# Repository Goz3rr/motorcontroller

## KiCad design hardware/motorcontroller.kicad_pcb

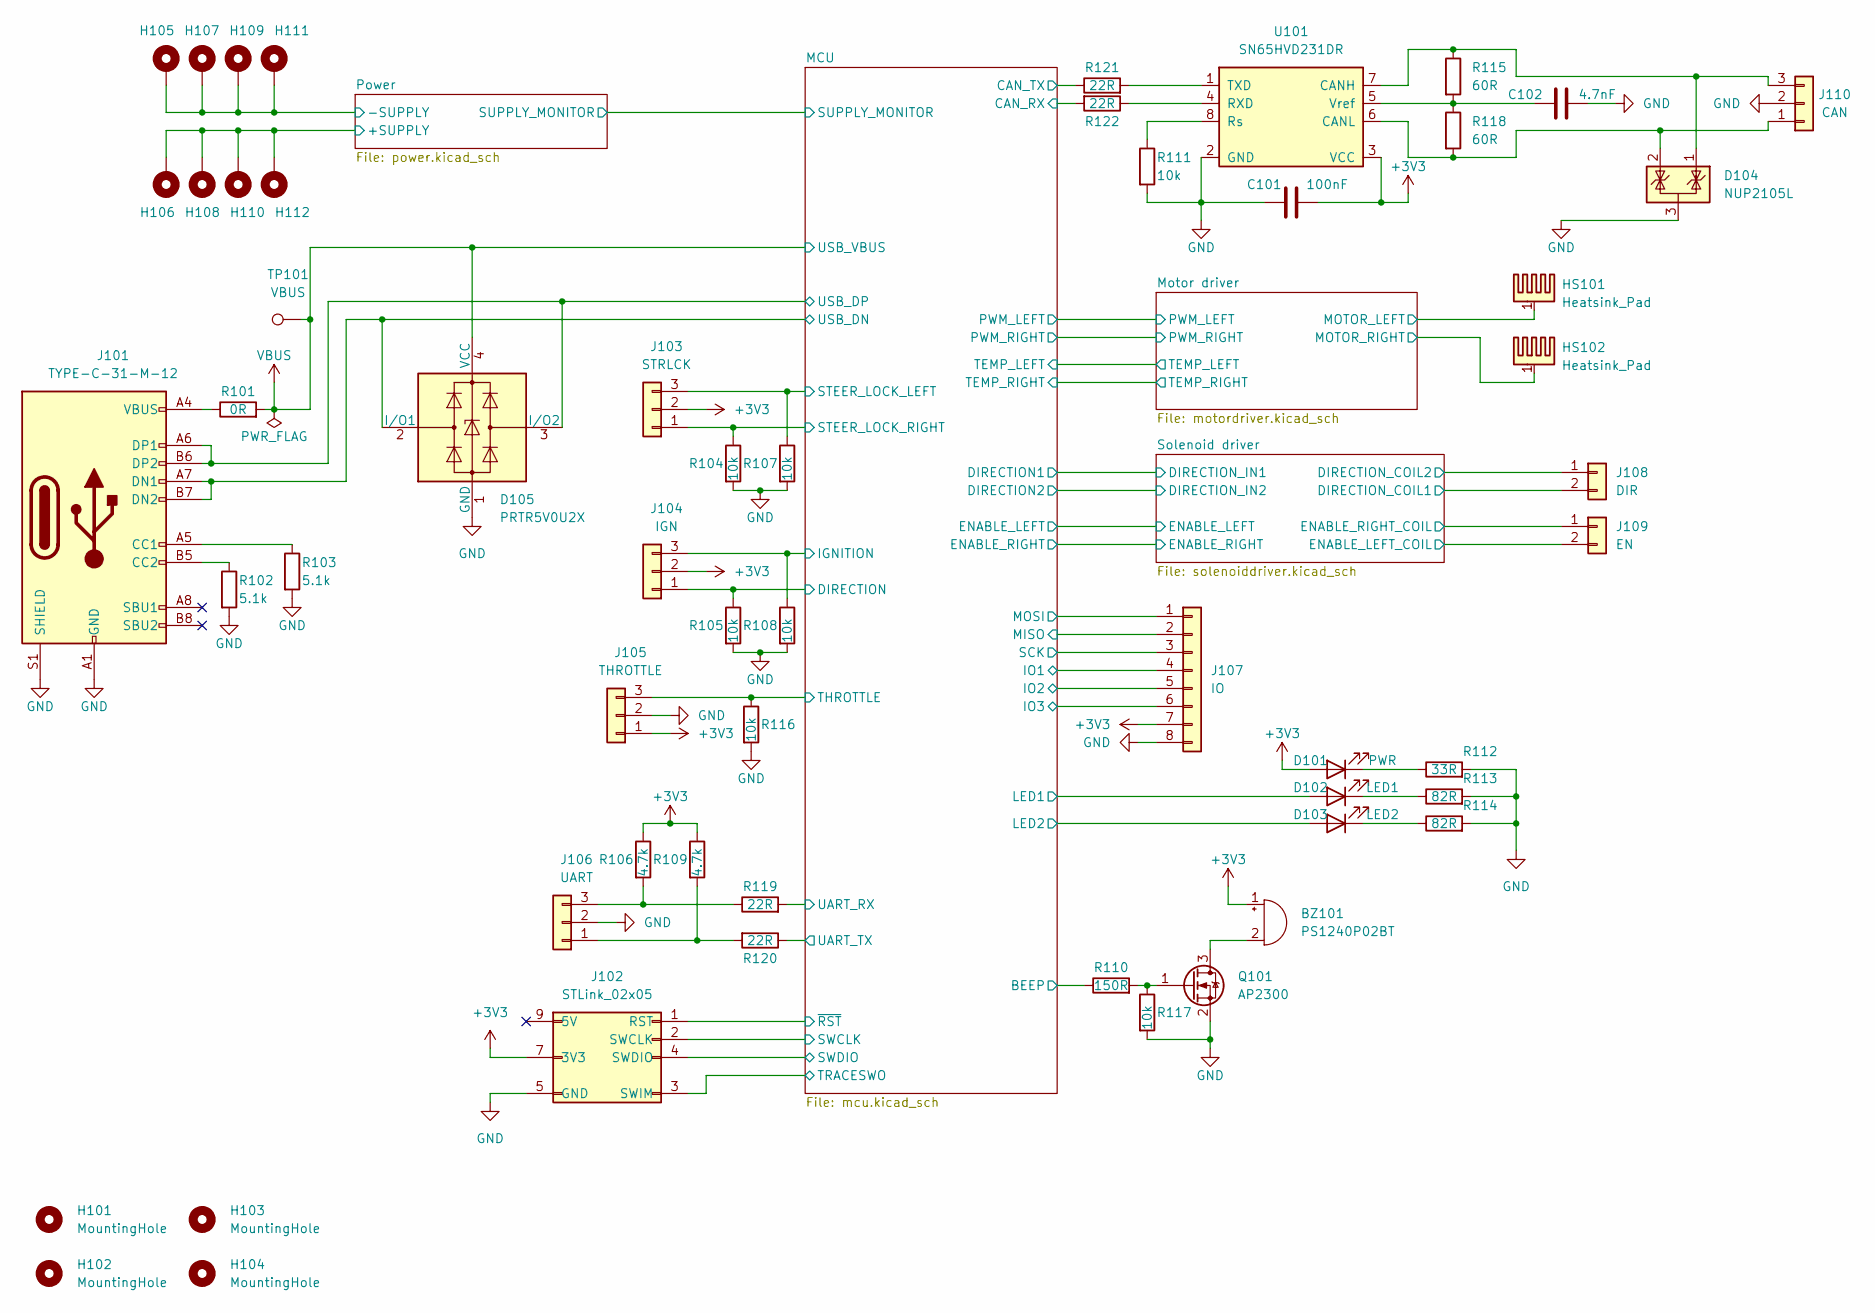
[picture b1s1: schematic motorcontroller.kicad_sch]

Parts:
BZ101: PS1240P02BT; Buzzer_TDK_PS1240P02BT_D12.2mm_H6.5mm
C101: 100nF; C_0603_1608Metric_Pad1.08x0.95mm_HandSolder
C102: 4.7nF; C_0603_1608Metric_Pad1.08x0.95mm_HandSolder
D101: PWR; LED_0805_2012Metric_Pad1.15x1.40mm_HandSolder
D102: LED1; LED_0805_2012Metric_Pad1.15x1.40mm_HandSolder
D103: LED2; LED_0805_2012Metric_Pad1.15x1.40mm_HandSolder
D104: NUP2105L; SOT-23
D105: PRTR5V0U2X; SOT-143
H101, H102, H103, H104: MountingHole; MountingHole_3.2mm_M3
H105, H106, H107, H108, H109, H110, H111, H112: MountingHole_Pad; MountingHole_4.3mm_M4_Pad
HS101, HS102: Heatsink_Pad
J101: TYPE-C-31-M-12; USB_C_Receptacle_HRO_TYPE-C-31-M-12_Handsoldering
J102: STLink_02x05; PinHeader_2x05_P2.54mm_Vertical
J103: STRLCK; JST_XH_B3B-XH-A_1x03_P2.50mm_Vertical
J104: IGN; JST_XH_B3B-XH-A_1x03_P2.50mm_Vertical
J105: THROTTLE; JST_XH_B3B-XH-A_1x03_P2.50mm_Vertical
J106: UART; PinHeader_1x03_P2.54mm_Vertical
J107: IO; PinHeader_1x08_P2.54mm_Vertical
J108: DIR; JST_XH_B2B-XH-A_1x02_P2.50mm_Vertical
J109: EN; JST_XH_B2B-XH-A_1x02_P2.50mm_Vertical
J110: CAN; JST_XH_B3B-XH-A_1x03_P2.50mm_Vertical
Q101: AP2300; TSOT-23_HandSoldering
R101: 0R; R_0603_1608Metric_Pad0.98x0.95mm_HandSolder
R102, R103: 5.1k; R_0603_1608Metric_Pad0.98x0.95mm_HandSolder
R104, R105, R107, R108, R111, R116, R117: 10k; R_0603_1608Metric_Pad0.98x0.95mm_HandSolder
R106, R109: 4.7k; R_0603_1608Metric_Pad0.98x0.95mm_HandSolder
R110: 150R; R_0603_1608Metric_Pad0.98x0.95mm_HandSolder
R112: 33R; R_0603_1608Metric_Pad0.98x0.95mm_HandSolder
R113, R114: 82R; R_0603_1608Metric_Pad0.98x0.95mm_HandSolder
R115, R118: 60R; R_0603_1608Metric_Pad0.98x0.95mm_HandSolder
R119, R120, R121, R122: 22R; R_0603_1608Metric_Pad0.98x0.95mm_HandSolder
TP101: VBUS; TestPoint_Pad_D2.0mm
U101: SN65HVD231DR; SOIC-8_3.9x4.9mm_P1.27mm

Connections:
+3V3: BZ101.1 (-), C101.2, D101.2 (A), J102.7 (3V3), J102.8 (3V3), J103.2, J104.2, J105.1, J107.7, R106.1, R109.1, U101.3 (VCC); also elsewhere on the board
+BATT: H106.1, H108.1, H110.1, H112.1; also elsewhere on the board
/MCU/BEEP: R110.1; also elsewhere on the board
/MCU/CAN_RX: R122.2; also elsewhere on the board
/MCU/CAN_TX: R121.1; also elsewhere on the board
/MCU/DIRECTION: J104.1, R105.1; also elsewhere on the board
/MCU/IGNITION: J104.3, R108.1; also elsewhere on the board
/MCU/IO1: J107.4; also elsewhere on the board
/MCU/IO2: J107.5; also elsewhere on the board
/MCU/IO3: J107.6; also elsewhere on the board
/MCU/LED1: D102.2 (A); also elsewhere on the board
/MCU/LED2: D103.2 (A); also elsewhere on the board
/MCU/MISO: J107.2; also elsewhere on the board
/MCU/MOSI: J107.1; also elsewhere on the board
/MCU/SCK: J107.3; also elsewhere on the board
/MCU/STEER_LOCK_LEFT: J103.3, R107.1; also elsewhere on the board
/MCU/STEER_LOCK_RIGHT: J103.1, R104.1; also elsewhere on the board
/MCU/SWCLK: J102.2 (SWCLK); also elsewhere on the board
/MCU/SWDIO: J102.4 (SWDIO); also elsewhere on the board
/MCU/THROTTLE: J105.3, R116.1; also elsewhere on the board
/MCU/TRACESWO: J102.3 (SWIM); also elsewhere on the board
/MCU/UART_RX: R119.2; also elsewhere on the board
/MCU/UART_TX: R120.1; also elsewhere on the board
/MCU/USB_DN: D105.2 (I/O1), J101.A7 (DN1), J101.B7 (DN2); also elsewhere on the board
/MCU/USB_DP: D105.3 (I/O2), J101.A6 (DP1), J101.B6 (DP2); also elsewhere on the board
/MCU/~RST: J102.1 (RST); also elsewhere on the board
/Solenoid driver/DIRECTION_COIL1: J108.2; also elsewhere on the board
/Solenoid driver/DIRECTION_COIL2: J108.1; also elsewhere on the board
/Solenoid driver/ENABLE_LEFT_COIL: J109.2; also elsewhere on the board
/Solenoid driver/ENABLE_RIGHT_COIL: J109.1; also elsewhere on the board
GND: C101.1, C102.2, D104.3 (A), D105.1 (GND), H105.1, H107.1, H109.1, H111.1, J101.A1 (GND), J101.A12 (GND), J101.B1 (GND), J101.B12 (GND), J101.S1 (SHIELD), J102.5 (GND), J102.6 (GND), J105.2, J106.2, J107.8, J110.2, Q101.2 (S), R102.2, R103.2, R104.2, R105.2, R107.2, R108.2, R111.2, R112.2, R113.2, R114.2, R116.2, R117.2, U101.2 (GND); also elsewhere on the board
unnamed: BZ101.2 (+), Q101.3 (D)
unnamed: C102.1, R115.2, R118.1, U101.5 (Vref)
unnamed: D101.1 (K), R112.1
unnamed: D102.1 (K), R113.1
unnamed: D103.1 (K), R114.1
unnamed: D104.1 (K), J110.3, R115.1, U101.7 (CANH)
unnamed: D104.2 (K), J110.1, R118.2, U101.6 (CANL)
unnamed: J101.A4 (VBUS), J101.A9 (VBUS), J101.B4 (VBUS), J101.B9 (VBUS), R101.1
unnamed: J101.A5 (CC1), R103.1
unnamed: J101.B5 (CC2), R102.1
unnamed: J106.1, R109.2, R120.2
unnamed: J106.3, R106.2, R119.1
unnamed: Q101.1 (G), R110.2, R117.1
unnamed: R111.1, U101.8 (Rs)
unnamed: R121.2, U101.1 (TXD)
unnamed: R122.1, U101.4 (RXD)
VBUS: D105.4 (VCC), R101.2, TP101.1; also elsewhere on the board

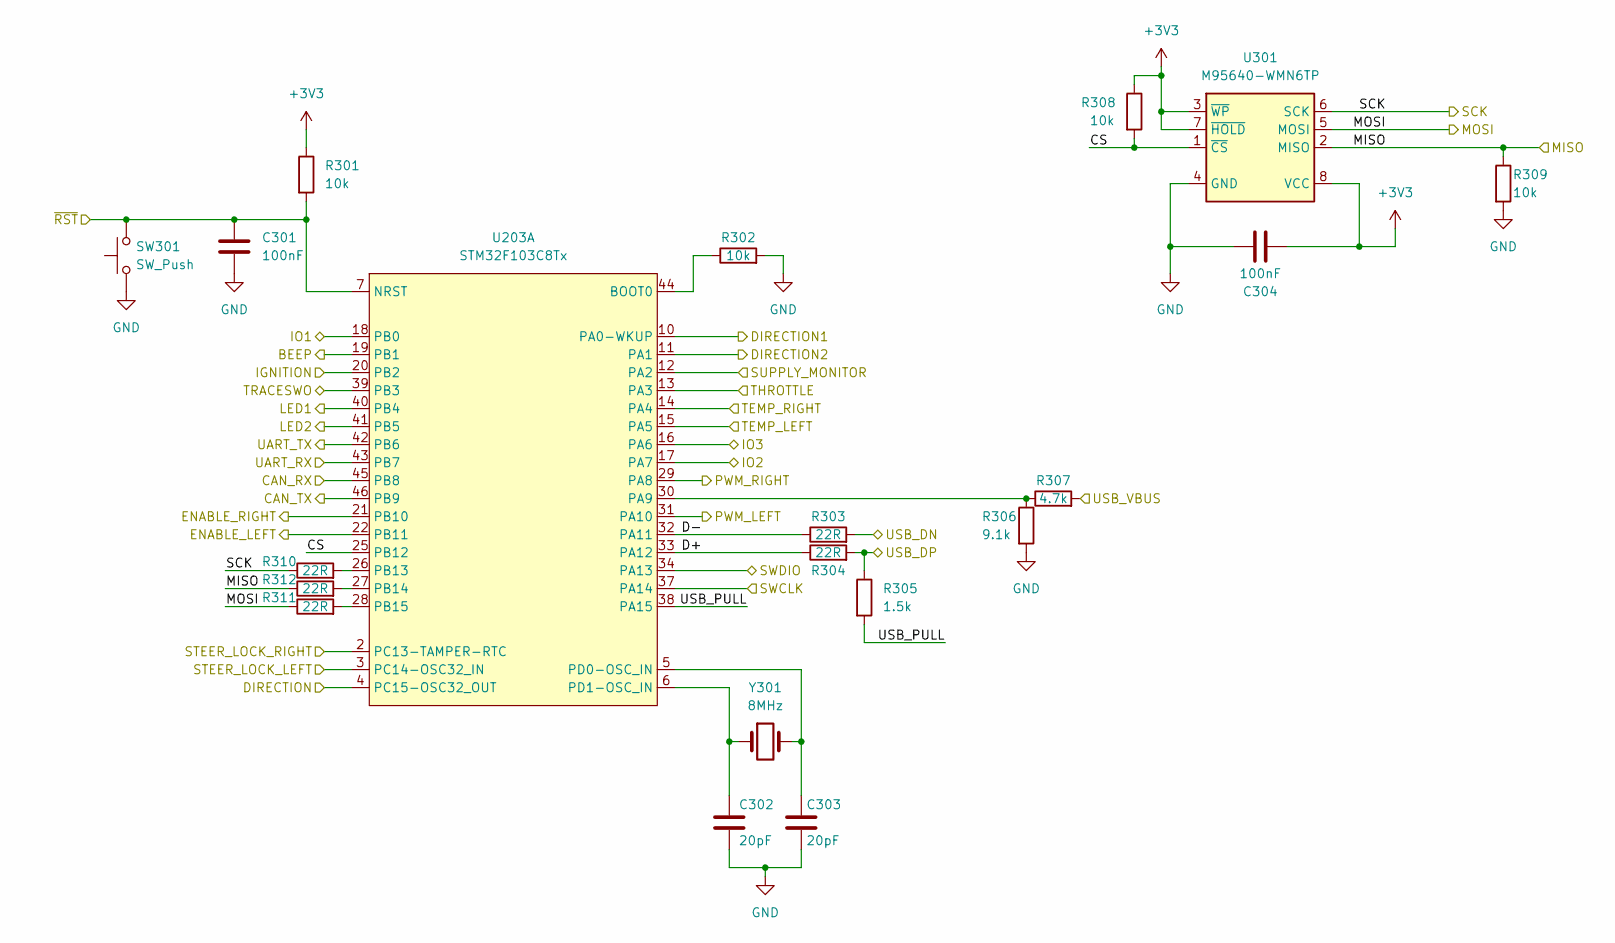
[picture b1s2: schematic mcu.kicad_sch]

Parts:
C301, C304: 100nF; C_0603_1608Metric_Pad1.08x0.95mm_HandSolder
C302, C303: 20pF; C_0603_1608Metric_Pad1.08x0.95mm_HandSolder
R301, R302, R308, R309: 10k; R_0603_1608Metric_Pad0.98x0.95mm_HandSolder
R303, R304, R310, R311, R312: 22R; R_0603_1608Metric_Pad0.98x0.95mm_HandSolder
R305: 1.5k; R_0603_1608Metric_Pad0.98x0.95mm_HandSolder
R306: 9.1k; R_0603_1608Metric_Pad0.98x0.95mm_HandSolder
R307: 4.7k; R_0603_1608Metric_Pad0.98x0.95mm_HandSolder
SW301: SW_Push; SW_SPST_TS-1185EC
U203: STM32F103C8Tx; LQFP-48_7x7mm_P0.5mm
U301: M95640-WMN6TP; SOIC-8_3.9x4.9mm_P1.27mm
Y301: 8MHz; Crystal_SMD_5032-2Pin_5.0x3.2mm_HandSoldering

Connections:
+3V3: C304.1, R301.1, R308.1, U301.3 (~WP), U301.7 (~HOLD), U301.8 (VCC); also elsewhere on the board
/MCU/BEEP: U203.19 (PB1); also elsewhere on the board
/MCU/CAN_RX: U203.45 (PB8); also elsewhere on the board
/MCU/CAN_TX: U203.46 (PB9); also elsewhere on the board
/MCU/CS: R308.2, U203.25 (PB12), U301.1 (~CS)
/MCU/D+: R304.1, U203.33 (PA12)
/MCU/D-: R303.1, U203.32 (PA11)
/MCU/DIRECTION: U203.4 (PC15-OSC32_OUT); also elsewhere on the board
/MCU/DIRECTION1: U203.10 (PA0-WKUP); also elsewhere on the board
/MCU/DIRECTION2: U203.11 (PA1); also elsewhere on the board
/MCU/ENABLE_LEFT: U203.22 (PB11); also elsewhere on the board
/MCU/ENABLE_RIGHT: U203.21 (PB10); also elsewhere on the board
/MCU/IGNITION: U203.20 (PB2); also elsewhere on the board
/MCU/IO1: U203.18 (PB0); also elsewhere on the board
/MCU/IO2: U203.17 (PA7); also elsewhere on the board
/MCU/IO3: U203.16 (PA6); also elsewhere on the board
/MCU/LED1: U203.40 (PB4); also elsewhere on the board
/MCU/LED2: U203.41 (PB5); also elsewhere on the board
/MCU/MISO: R309.1, R312.1, U301.2 (MISO); also elsewhere on the board
/MCU/MOSI: R311.1, U301.5 (MOSI); also elsewhere on the board
/MCU/PWM_LEFT: U203.31 (PA10); also elsewhere on the board
/MCU/PWM_RIGHT: U203.29 (PA8); also elsewhere on the board
/MCU/SCK: R310.1, U301.6 (SCK); also elsewhere on the board
/MCU/STEER_LOCK_LEFT: U203.3 (PC14-OSC32_IN); also elsewhere on the board
/MCU/STEER_LOCK_RIGHT: U203.2 (PC13-TAMPER-RTC); also elsewhere on the board
/MCU/SUPPLY_MONITOR: U203.12 (PA2); also elsewhere on the board
/MCU/SWCLK: U203.37 (PA14); also elsewhere on the board
/MCU/SWDIO: U203.34 (PA13); also elsewhere on the board
/MCU/TEMP_LEFT: U203.15 (PA5); also elsewhere on the board
/MCU/TEMP_RIGHT: U203.14 (PA4); also elsewhere on the board
/MCU/THROTTLE: U203.13 (PA3); also elsewhere on the board
/MCU/TRACESWO: U203.39 (PB3); also elsewhere on the board
/MCU/UART_RX: U203.43 (PB7); also elsewhere on the board
/MCU/UART_TX: U203.42 (PB6); also elsewhere on the board
/MCU/USB_DN: R303.2; also elsewhere on the board
/MCU/USB_DP: R304.2, R305.1; also elsewhere on the board
/MCU/USB_PULL: R305.2, U203.38 (PA15)
/MCU/~RST: C301.1, R301.2, SW301.2, U203.7 (NRST); also elsewhere on the board
GND: C301.2, C302.2, C303.2, C304.2, R302.2, R306.2, R309.2, SW301.1, U301.4 (GND); also elsewhere on the board
unnamed: C302.1, U203.6 (PD1-OSC_IN), Y301.1
unnamed: C303.1, U203.5 (PD0-OSC_IN), Y301.2
unnamed: R302.1, U203.44 (BOOT0)
unnamed: R306.1, R307.1, U203.30 (PA9)
unnamed: R310.2, U203.26 (PB13)
unnamed: R311.2, U203.28 (PB15)
unnamed: R312.2, U203.27 (PB14)
VBUS: R307.2; also elsewhere on the board

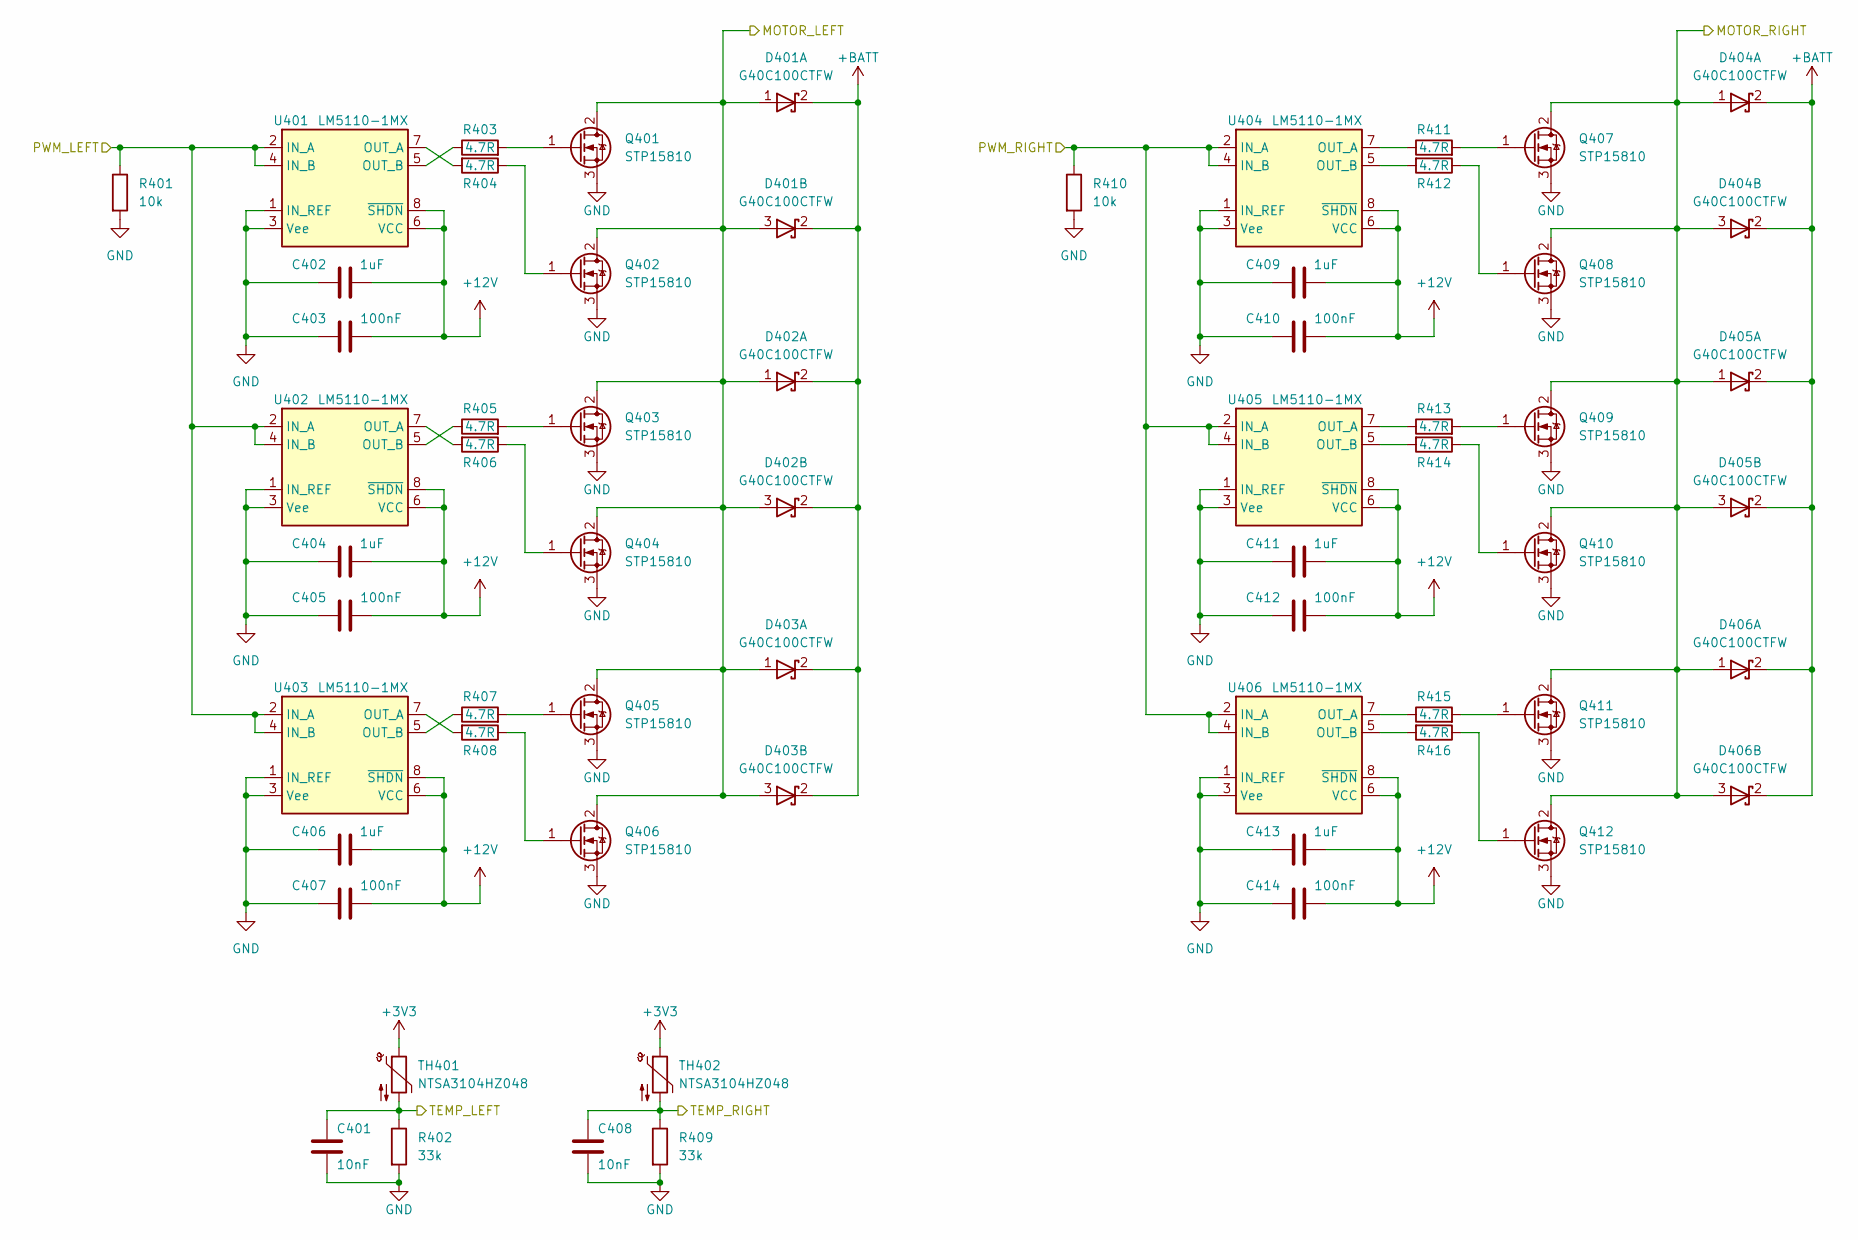
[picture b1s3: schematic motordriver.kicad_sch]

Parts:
C401, C408: 10nF; C_0603_1608Metric_Pad1.08x0.95mm_HandSolder
C402, C404, C406, C409, C411, C413: 1uF; C_0603_1608Metric_Pad1.08x0.95mm_HandSolder
C403, C405, C407, C410, C412, C414: 100nF; C_0603_1608Metric_Pad1.08x0.95mm_HandSolder
D401, D402, D403, D404, D405, D406: G40C100CTFW; TO-220F-3_Vertical
Q401, Q402, Q403, Q404, Q405, Q406, Q407, Q408, Q409, Q410, Q411, Q412: STP15810; TO-220-3_Vertical
R401, R410: 10k; R_0603_1608Metric_Pad0.98x0.95mm_HandSolder
R402, R409: 33k; R_0603_1608Metric_Pad0.98x0.95mm_HandSolder
R403, R404, R405, R406, R407, R408, R411, R412, R413, R414, R415, R416: 4.7R; R_0603_1608Metric_Pad0.98x0.95mm_HandSolder
TH401, TH402: NTSA3104HZ048; R_Axial_DIN0309_L9.0mm_D3.2mm_P2.54mm_Vertical
U401, U402, U403, U404, U405, U406: LM5110-1MX; SOIC-8_3.9x4.9mm_P1.27mm

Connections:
+3V3: TH401.1, TH402.1; also elsewhere on the board
+12V: C402.2, C403.2, C404.2, C405.2, C406.2, C407.2, C409.2, C410.2, C411.2, C412.2, C413.2, C414.2, U401.6 (VCC), U401.8 (~SHDN), U402.6 (VCC), U402.8 (~SHDN), U403.6 (VCC), U403.8 (~SHDN), U404.6 (VCC), U404.8 (~SHDN), U405.6 (VCC), U405.8 (~SHDN), U406.6 (VCC), U406.8 (~SHDN); also elsewhere on the board
+BATT: D401.2 (K), D402.2 (K), D403.2 (K), D404.2 (K), D405.2 (K), D406.2 (K); also elsewhere on the board
/MCU/PWM_LEFT: R401.1, U401.2 (IN_A), U401.4 (IN_B), U402.2 (IN_A), U402.4 (IN_B), U403.2 (IN_A), U403.4 (IN_B); also elsewhere on the board
/MCU/PWM_RIGHT: R410.1, U404.2 (IN_A), U404.4 (IN_B), U405.2 (IN_A), U405.4 (IN_B), U406.2 (IN_A), U406.4 (IN_B); also elsewhere on the board
/MCU/TEMP_LEFT: C401.1, R402.1, TH401.2; also elsewhere on the board
/MCU/TEMP_RIGHT: C408.1, R409.1, TH402.2; also elsewhere on the board
/Motor driver/MOTOR_LEFT: D401.1 (A), D401.3 (K), D402.1 (A), D402.3 (K), D403.1 (A), D403.3 (K), Q401.2 (D), Q402.2 (D), Q403.2 (D), Q404.2 (D), Q405.2 (D), Q406.2 (D)
/Motor driver/MOTOR_RIGHT: D404.1 (A), D404.3 (K), D405.1 (A), D405.3 (K), D406.1 (A), D406.3 (K), Q407.2 (D), Q408.2 (D), Q409.2 (D), Q410.2 (D), Q411.2 (D), Q412.2 (D)
GND: C401.2, C402.1, C403.1, C404.1, C405.1, C406.1, C407.1, C408.2, C409.1, C410.1, C411.1, C412.1, C413.1, C414.1, Q401.3 (S), Q402.3 (S), Q403.3 (S), Q404.3 (S), Q405.3 (S), Q406.3 (S), Q407.3 (S), Q408.3 (S), Q409.3 (S), Q410.3 (S), Q411.3 (S), Q412.3 (S), R401.2, R402.2, R409.2, R410.2, U401.1 (IN_REF), U401.3 (Vee), U402.1 (IN_REF), U402.3 (Vee), U403.1 (IN_REF), U403.3 (Vee), U404.1 (IN_REF), U404.3 (Vee), U405.1 (IN_REF), U405.3 (Vee), U406.1 (IN_REF), U406.3 (Vee); also elsewhere on the board
unnamed: Q401.1 (G), R403.2
unnamed: Q402.1 (G), R404.1
unnamed: Q403.1 (G), R405.2
unnamed: Q404.1 (G), R406.1
unnamed: Q405.1 (G), R407.2
unnamed: Q406.1 (G), R408.1
unnamed: Q407.1 (G), R411.2
unnamed: Q408.1 (G), R412.1
unnamed: Q409.1 (G), R413.2
unnamed: Q410.1 (G), R414.1
unnamed: Q411.1 (G), R415.2
unnamed: Q412.1 (G), R416.1
unnamed: R403.1, U401.5 (OUT_B)
unnamed: R404.2, U401.7 (OUT_A)
unnamed: R405.1, U402.5 (OUT_B)
unnamed: R406.2, U402.7 (OUT_A)
unnamed: R407.1, U403.5 (OUT_B)
unnamed: R408.2, U403.7 (OUT_A)
unnamed: R411.1, U404.7 (OUT_A)
unnamed: R412.2, U404.5 (OUT_B)
unnamed: R413.1, U405.7 (OUT_A)
unnamed: R414.2, U405.5 (OUT_B)
unnamed: R415.1, U406.7 (OUT_A)
unnamed: R416.2, U406.5 (OUT_B)

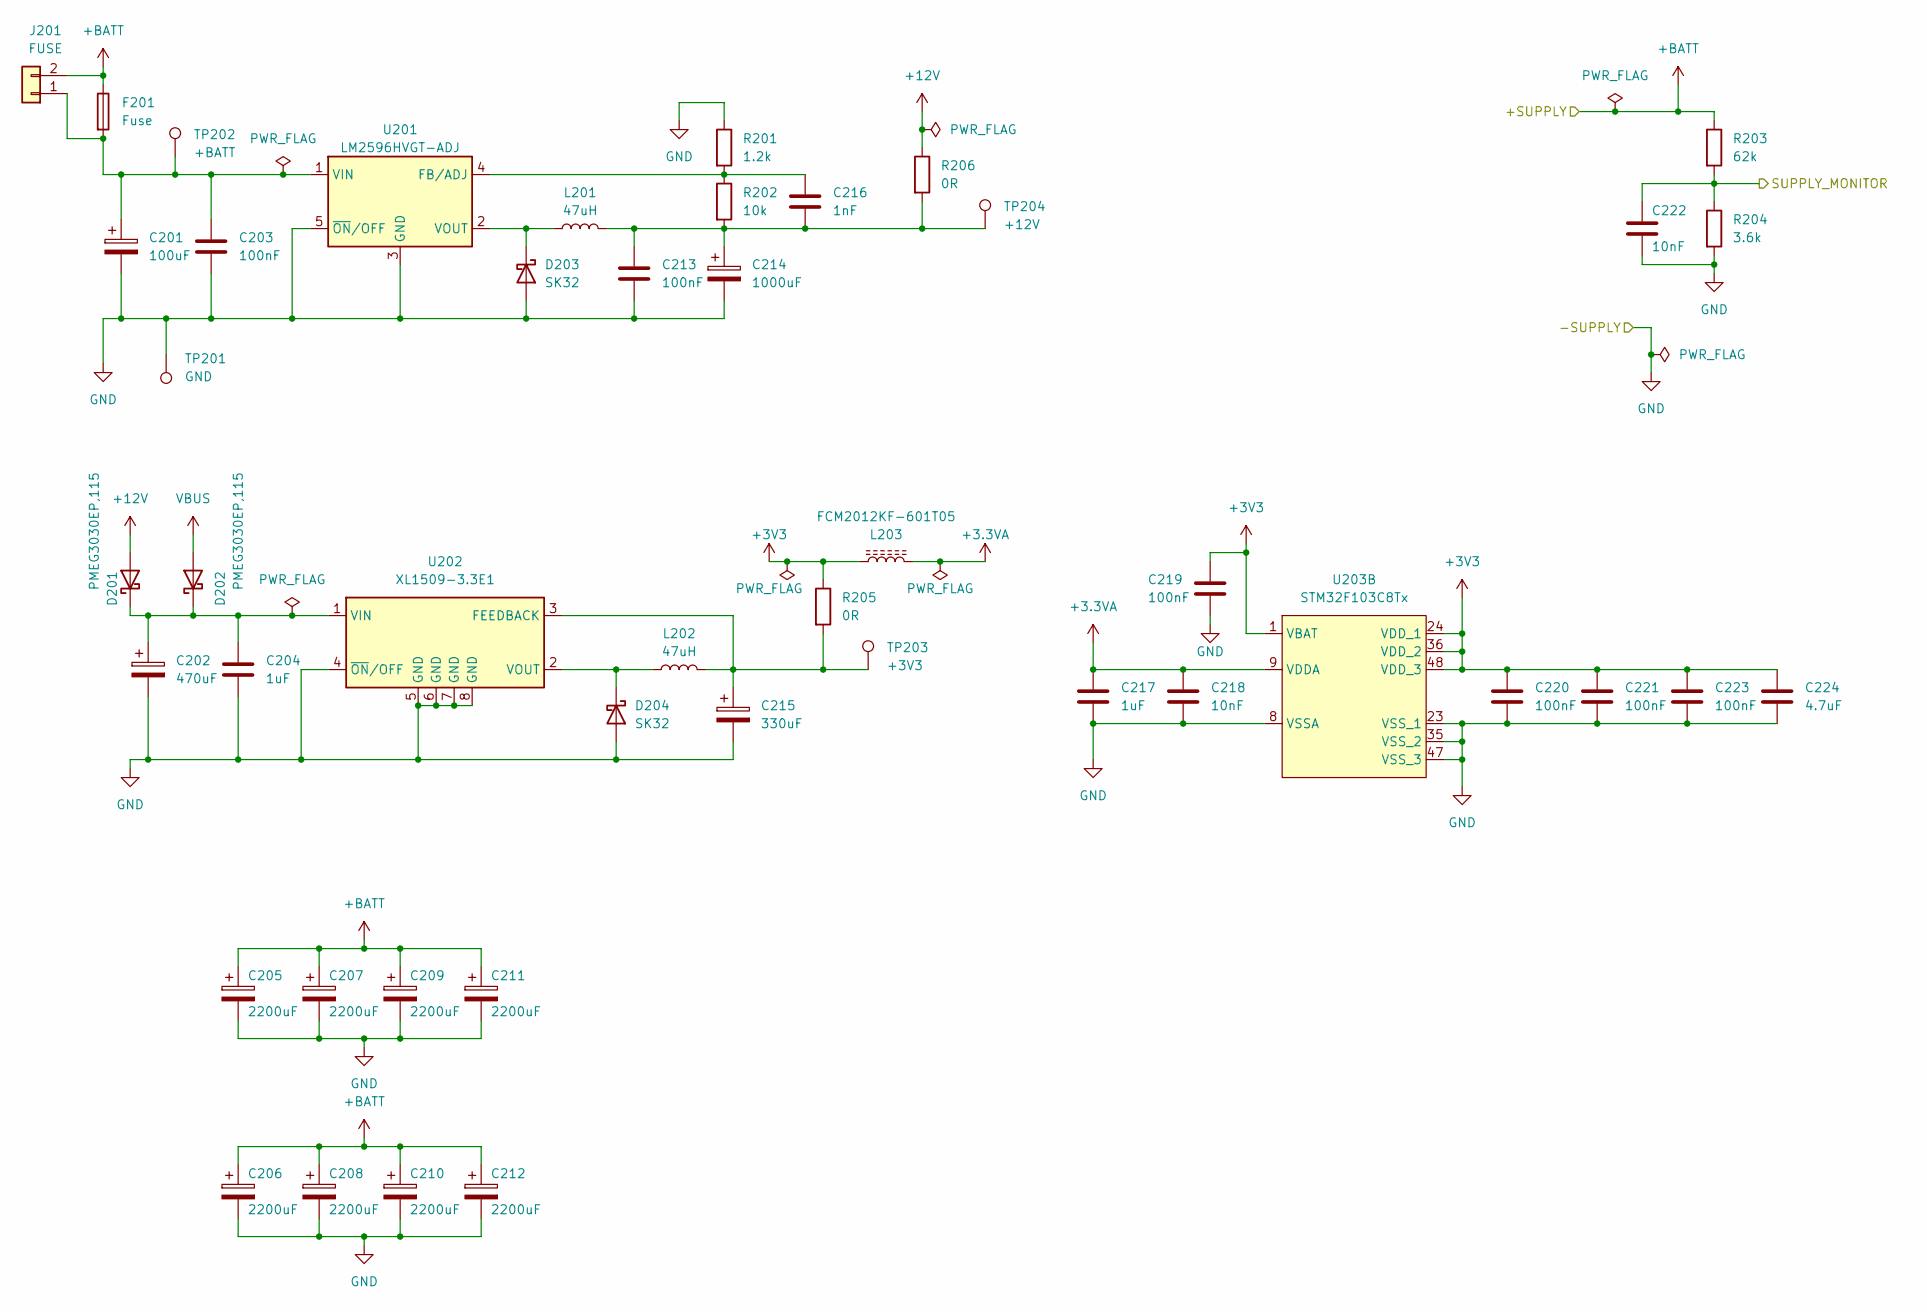
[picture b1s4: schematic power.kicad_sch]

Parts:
C201: 100uF; CP_Radial_D8.0mm_P3.50mm
C202: 470uF; CP_Elec_8x10.5
C203, C213, C219, C220, C221, C223: 100nF; C_0603_1608Metric_Pad1.08x0.95mm_HandSolder
C204, C217: 1uF; C_0603_1608Metric_Pad1.08x0.95mm_HandSolder
C205, C206, C207, C208, C209, C210, C211, C212: 2200uF; CP_Radial_D18.0mm_P7.50mm_P5.00mm
C214: 1000uF; CP_Radial_D10.0mm_P5.00mm
C215: 330uF; CP_Elec_6.3x5.4
C216: 1nF; C_0603_1608Metric_Pad1.08x0.95mm_HandSolder
C218, C222: 10nF; C_0603_1608Metric_Pad1.08x0.95mm_HandSolder
C224: 4.7uF; C_0603_1608Metric_Pad1.08x0.95mm_HandSolder
D201, D202: PMEG3030EP,115; D_SOD-128
D203, D204: SK32; D_SOD-123F
F201: Fuse; Fuseholder_Littelfuse_Nano2_154x
J201: FUSE; JST_XH_B2B-XH-A_1x02_P2.50mm_Vertical
L201: 47uH; L_10.4x10.4_H4.8_Handsoldering
L202: 47uH; L_YNR6045
L203: FCM2012KF-601T05; L_0805_2012Metric_Pad1.15x1.40mm_HandSolder
R201: 1.2k; R_0603_1608Metric_Pad0.98x0.95mm_HandSolder
R202: 10k; R_0603_1608Metric_Pad0.98x0.95mm_HandSolder
R203: 62k; R_0603_1608Metric_Pad0.98x0.95mm_HandSolder
R204: 3.6k; R_0603_1608Metric_Pad0.98x0.95mm_HandSolder
R205, R206: 0R; R_0603_1608Metric_Pad0.98x0.95mm_HandSolder
TP201: GND; TestPoint_Pad_D2.0mm
TP202: +BATT; TestPoint_Pad_D2.0mm
TP203: +3V3; TestPoint_Pad_D2.0mm
TP204: +12V; TestPoint_Pad_D2.0mm
U201: LM2596HVGT-ADJ; TO-220-5_Vertical
U202: XL1509-3.3E1; SOP-8_3.76x4.96mm_P1.27mm
U203: STM32F103C8Tx; LQFP-48_7x7mm_P0.5mm

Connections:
+3.3VA: C217.1, C218.1, L203.2, U203.9 (VDDA)
+3V3: C219.2, C220.1, C221.1, C223.1, C224.1, L203.1, R205.1, U203.1 (VBAT), U203.24 (VDD_1), U203.36 (VDD_2), U203.48 (VDD_3); also elsewhere on the board
+12V: D201.2 (A), R206.1; also elsewhere on the board
+BATT: C205.1, C206.1, C207.1, C208.1, C209.1, C210.1, C211.1, C212.1, F201.1, J201.2, R203.1; also elsewhere on the board
/MCU/SUPPLY_MONITOR: C222.1, R203.2, R204.1; also elsewhere on the board
GND: C201.2, C202.2, C203.2, C204.2, C205.2, C206.2, C207.2, C208.2, C209.2, C210.2, C211.2, C212.2, C213.2, C214.2, C215.2, C217.2, C218.2, C219.1, C220.2, C221.2, C222.2, C223.2, C224.2, D203.2 (A), D204.2 (A), R201.1, R204.2, TP201.1, U201.3 (GND), U201.5 (~ON/OFF), U202.4 (~ON/OFF), U202.5 (GND), U202.6 (GND), U202.7 (GND), U202.8 (GND), U203.8 (VSSA), U203.23 (VSS_1), U203.35 (VSS_2), U203.47 (VSS_3); also elsewhere on the board
unnamed: C201.1, C203.1, F201.2, J201.1, TP202.1, U201.1 (VIN)
unnamed: C202.1, C204.1, D201.1 (K), D202.1 (K), U202.1 (VIN)
unnamed: C213.1, C214.1, C216.2, L201.2, R202.2, R206.2, TP204.1
unnamed: C215.1, L202.2, R205.2, TP203.1, U202.3 (FEEDBACK)
unnamed: C216.1, R201.2, R202.1, U201.4 (FB/ADJ)
unnamed: D203.1 (K), L201.1, U201.2 (VOUT)
unnamed: D204.1 (K), L202.1, U202.2 (VOUT)
VBUS: D202.2 (A); also elsewhere on the board

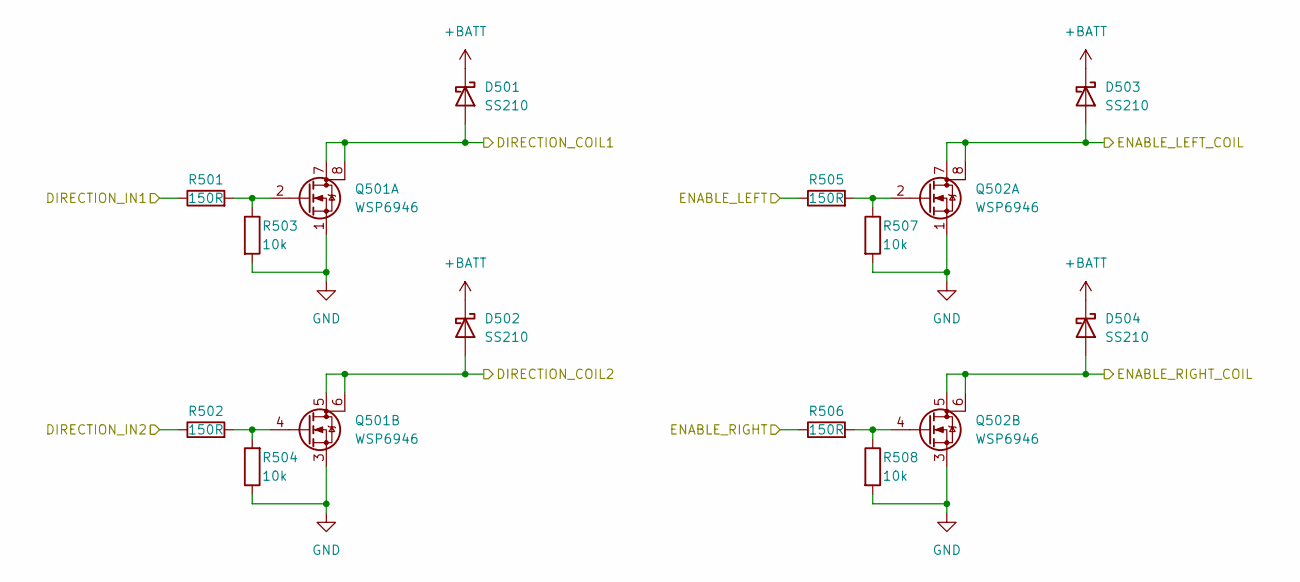
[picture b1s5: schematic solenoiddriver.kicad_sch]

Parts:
D501, D502, D503, D504: SS210; D_SMA_Handsoldering
Q501, Q502: WSP6946; SOP-8_3.9x4.9mm_P1.27mm
R501, R502, R505, R506: 150R; R_0603_1608Metric_Pad0.98x0.95mm_HandSolder
R503, R504, R507, R508: 10k; R_0603_1608Metric_Pad0.98x0.95mm_HandSolder

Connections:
+BATT: D501.1 (K), D502.1 (K), D503.1 (K), D504.1 (K); also elsewhere on the board
/MCU/DIRECTION1: R501.1; also elsewhere on the board
/MCU/DIRECTION2: R502.1; also elsewhere on the board
/MCU/ENABLE_LEFT: R505.1; also elsewhere on the board
/MCU/ENABLE_RIGHT: R506.1; also elsewhere on the board
/Solenoid driver/DIRECTION_COIL1: D501.2 (A), Q501.7 (D), Q501.8 (D); also elsewhere on the board
/Solenoid driver/DIRECTION_COIL2: D502.2 (A), Q501.5 (D), Q501.6 (D); also elsewhere on the board
/Solenoid driver/ENABLE_LEFT_COIL: D503.2 (A), Q502.7 (D), Q502.8 (D); also elsewhere on the board
/Solenoid driver/ENABLE_RIGHT_COIL: D504.2 (A), Q502.5 (D), Q502.6 (D); also elsewhere on the board
GND: Q501.1 (S), Q501.3 (S), Q502.1 (S), Q502.3 (S), R503.2, R504.1, R507.2, R508.2; also elsewhere on the board
unnamed: Q501.2 (G), R501.2, R503.1
unnamed: Q501.4 (G), R502.2, R504.2
unnamed: Q502.2 (G), R505.2, R507.1
unnamed: Q502.4 (G), R506.2, R508.1

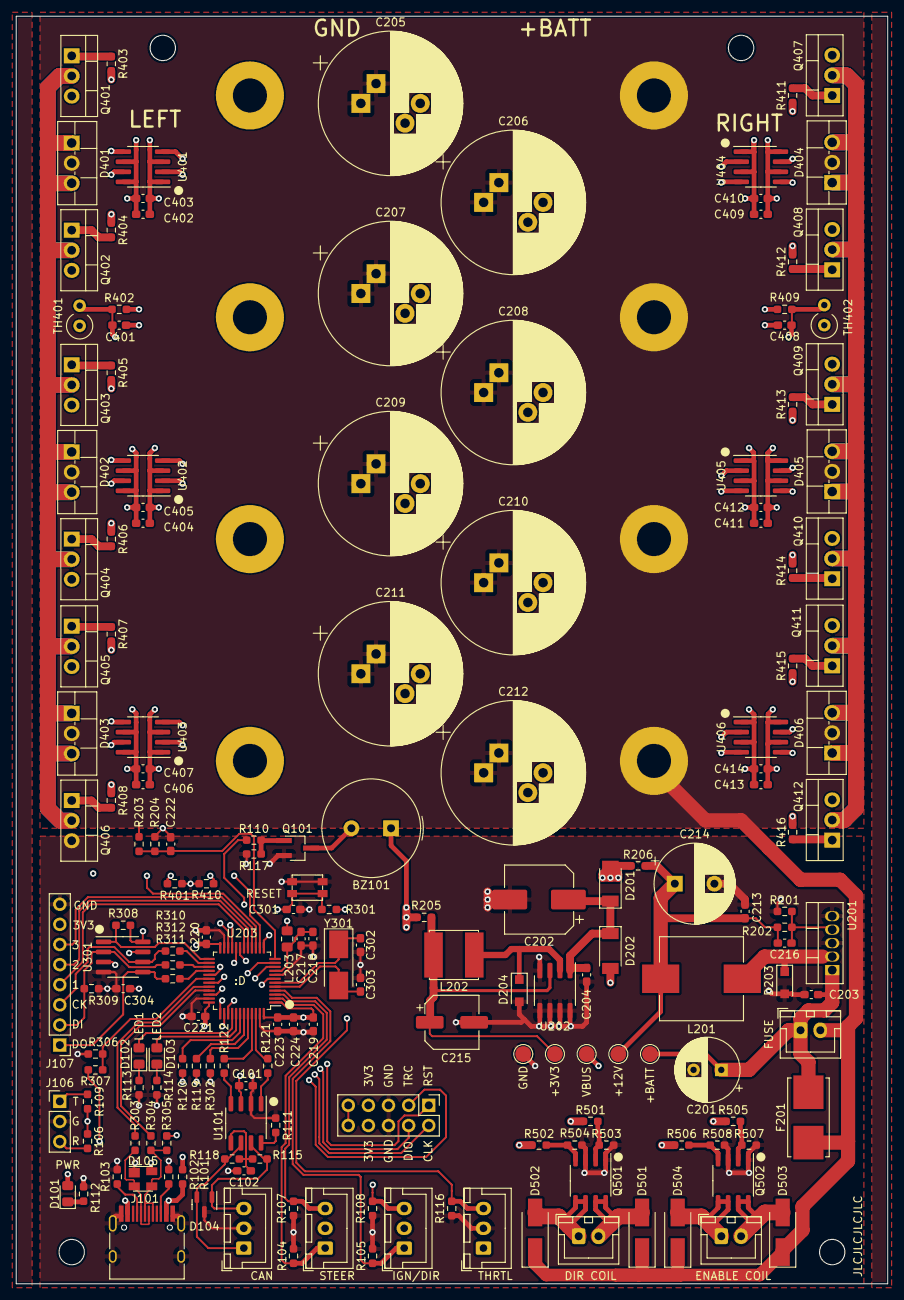
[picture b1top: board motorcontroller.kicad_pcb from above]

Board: 4 copper layers, 110.0 x 160.0 mm, 190 parts (0 on the bottom side), 107 nets.

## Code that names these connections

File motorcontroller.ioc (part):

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Mcu.Name=STM32F103C(8-B)Tx
Mcu.Package=LQFP48
Mcu.UserName=STM32F103C8Tx
PA0-WKUP.GPIOParameters=GPIO_Label
PA0-WKUP.GPIO_Label=DIRECTION1
PA0-WKUP.Signal=S_TIM2_CH1_ETR
PA1.GPIOParameters=GPIO_Label
PA1.GPIO_Label=DIRECTION2
PA1.Signal=S_TIM2_CH2
PA10.GPIOParameters=GPIO_Label
PA10.GPIO_Label=PWM_LEFT
PA10.Signal=S_TIM1_CH3
PA11.Mode=Device
PA11.Signal=USB_DM
PA12.Mode=Device
PA12.Signal=USB_DP
PA13.Mode=Trace_Asynchronous_SW
PA13.Signal=SYS_JTMS-SWDIO
PA14.Mode=Trace_Asynchronous_SW
PA14.Signal=SYS_JTCK-SWCLK
PA15.GPIOParameters=GPIO_Label
PA15.GPIO_Label=USB_PULL
PA15.Signal=GPIO_Output
PA2.GPIOParameters=GPIO_Label
PA2.GPIO_Label=SUPPLY_MONITOR
PA2.Signal=ADCx_IN2
PA3.GPIOParameters=GPIO_Label
PA3.GPIO_Label=THROTTLE
PA3.Signal=ADCx_IN3
PA4.GPIOParameters=GPIO_Label
PA4.GPIO_Label=TEMP_RIGHT
PA4.Signal=ADCx_IN4
PA5.GPIOParameters=GPIO_Label
PA5.GPIO_Label=TEMP_LEFT
PA5.Signal=ADCx_IN5
PA6.GPIOParameters=GPIO_Label
PA6.GPIO_Label=IO3
PA6.Signal=GPIO_Analog
PA7.GPIOParameters=GPIO_Label
PA7.GPIO_Label=IO2
PA7.Signal=GPIO_Analog
PA8.GPIOParameters=GPIO_Label
PA8.GPIO_Label=PWM_RIGHT
PA8.Signal=S_TIM1_CH1
PA9.GPIOParameters=GPIO_Label
PA9.GPIO_Label=USB_VBUS_DET
PA9.Signal=GPIO_Input
PB0.GPIOParameters=GPIO_Label
PB0.GPIO_Label=IO1
PB0.Signal=GPIO_Analog
PB1.GPIOParameters=GPIO_Label
PB1.GPIO_Label=BEEP
PB1.Signal=S_TIM3_CH4
PB10.GPIOParameters=GPIO_Label
PB10.GPIO_Label=ENABLE_LEFT
PB10.Signal=S_TIM2_CH3
PB11.GPIOParameters=GPIO_Label
PB11.GPIO_Label=ENABLE_RIGHT
PB11.Signal=S_TIM2_CH4
PB12.Mode=NSS_Signal_Hard_Output
PB12.Signal=SPI2_NSS
PB13.Mode=Full_Duplex_Master
PB13.Signal=SPI2_SCK
PB14.Mode=Full_Duplex_Master
PB14.Signal=SPI2_MISO
PB15.Mode=Full_Duplex_Master
PB15.Signal=SPI2_MOSI
PB2.GPIOParameters=GPIO_Label
PB2.GPIO_Label=IGNITION
PB2.Signal=GPIO_Input
PB3.Mode=Trace_Asynchronous_SW
PB3.Signal=SYS_JTDO-TRACESWO
PB4.GPIOParameters=GPIO_Label
PB4.GPIO_Label=LED1
PB4.Signal=GPIO_Output
PB5.GPIOParameters=GPIO_Label
PB5.GPIO_Label=LED2
PB5.Signal=GPIO_Output
PB6.Mode=Asynchronous
PB6.Signal=USART1_TX
PB7.Mode=Asynchronous
PB7.Signal=USART1_RX
PB8.Mode=CAN_Activate
PB8.Signal=CAN_RX
PB9.Mode=CAN_Activate
PB9.Signal=CAN_TX
PC13-TAMPER-RTC.GPIOParameters=GPIO_Label
PC13-TAMPER-RTC.GPIO_Label=STEER_LOCK_RIGHT
PC13-TAMPER-RTC.Signal=GPIO_Input
PC14-OSC32_IN.GPIOParameters=GPIO_Label
PC14-OSC32_IN.GPIO_Label=STEER_LOCK_LEFT
PC14-OSC32_IN.Signal=GPIO_Input
PC15-OSC32_OUT.GPIOParameters=GPIO_Label
PC15-OSC32_OUT.GPIO_Label=DIRECTION
PC15-OSC32_OUT.Signal=GPIO_Input
PD0-OSC_IN.Mode=HSE-External-Oscillator
PD0-OSC_IN.Signal=RCC_OSC_IN
PD1-OSC_OUT.Mode=HSE-External-Oscillator
PD1-OSC_OUT.Signal=RCC_OSC_OUT
RCC.SYSCLKFreq_VALUE=48000000
RCC.SYSCLKSource=RCC_SYSCLKSOURCE_PLLCLK
board=custom

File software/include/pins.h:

#pragma once

#include <libopencm3/stm32/gpio.h>

#define CPU_FREQ    72000000

// General IO
#define LED1_PORT   GPIOB
#define LED1_PIN    GPIO4
#define LED2_PORT   GPIOB
#define LED2_PIN    GPIO5

#define IO1_PORT    GPIOB
#define IO1_PIN     GPIO0
#define IO2_PORT    GPIOA
#define IO2_PIN     GPIO7
#define IO3_PORT    GPIOA
#define IO3_PIN     GPIO6


// Control
#define STEER_LEFT_PORT     GPIOC
#define STEER_LEFT_PIN      GPIO14
#define STEER_RIGHT_PORT    GPIOC
#define STEER_RIGHT_PIN     GPIO13

#define DIRECTION_PORT  GPIOC
#define DIRECTION_PIN   GPIO15

#define DIRECTION1_PORT GPIOA
#define DIRECTION1_PIN  GPIO0
#define DIRECTION2_PORT GPIOA
#define DIRECTION2_PIN  GPIO1

#define SUPPLY_MONITOR_PORT GPIOA
#define SUPPLY_MONITOR_PIN  GPIO2

#define THROTTLE_PORT   GPIOA
#define THROTTLE_PIN    GPIO3

#define TEMP_LEFT_PORT  GPIOA
#define TEMP_LEFT_PIN   GPIO5
#define TEMP_RIGHT_PORT GPIOA
#define TEMP_RIGHT_PIN  GPIO4

#define BEEP_PORT       GPIO_BANK_TIM3_CH4
#define BEEP_PIN        GPIO_TIM3_CH4

#define IGNITION_PORT   GPIOB
#define IGNITION_PIN    GPIO2

#define ENABLE_LEFT_PORT    GPIOB
#define ENABLE_LEFT_PIN     GPIO10
#define ENABLE_RIGHT_PORT   GPIOB
#define ENABLE_RIGHT_PIN    GPIO11

#define PWM_LEFT_PORT   GPIOA
#define PWM_LEFT_PIN    GPIO10
#define PWM_RIGHT_PORT  GPIOA
#define PWM_RIGHT_PIN   GPIO8

#define USB_VBUS_DET_PORT   GPIOA
#define USB_VBUS_DET_PIN    GPIO9
#define USB_DM_PORT         GPIOA
#define USB_DM_PIN          GPIO11
#define USB_DP_PORT         GPIOA
#define USB_DP_PIN          GPIO12
#define USB_PULL_PORT       GPIOA
#define USB_PULL_PIN        GPIO15


// Interfaces
#define UART_TX_PORT    GPIOB
#define UART_TX_PIN     GPIO6
#define UART_RX_PORT    GPIOB
#define UART_RX_PIN     GPIO7

#define CAN_TX_PORT GPIOB
#define CAN_TX_PIN  GPIO9
#define CAN_RX_PORT GPIOB
#define CAN_RX_PIN  GPIO8

#define SPI_CS_PORT     GPIOB
#define SPI_CS_PIN      GPIO12
#define SPI_CLK_PORT    GPIOB
#define SPI_CLK_PIN     GPIO13
#define SPI_MISO_PORT   GPIOB
#define SPI_MISO_PIN    GPIO14
#define SPI_MOSI_PORT   GPIOB
#define SPI_MOSI_PIN    GPIO15

#define SWDIO_PORT      GPIOA
#define SWDIO_PIN       GPIO13
#define SWCLK_PORT      GPIOA
#define SWCLK_PIN       GPIO14
#define TRACESWO_PORT   GPIOB
#define TRACESWO_PIN    GPIO3

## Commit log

2021-08-13 Initial schematic commit
2021-08-13 Annotate schematic
2021-08-14 Clean up BOM
2021-08-15 Assign footprints
2021-08-15 Change to smaller 12MHz crystal
2021-08-16 Start PCB
2021-08-16 First PCB commit
2021-08-17 Finish regulator layout
2021-08-18 Finish PCB
2021-08-18 Swap for isolated TO220 diodes
2021-08-19 M3 mounting holes
2021-08-20 Tweak PCB and add gerbers
2021-08-25 Adjust 3d models
2021-08-25 Move kicad files to hardware subfolder
2021-09-03 Change diode package to isolated TO220
2021-09-11 First code commit
2021-09-11 Fix pwm
2021-09-25 start solenoid driver
